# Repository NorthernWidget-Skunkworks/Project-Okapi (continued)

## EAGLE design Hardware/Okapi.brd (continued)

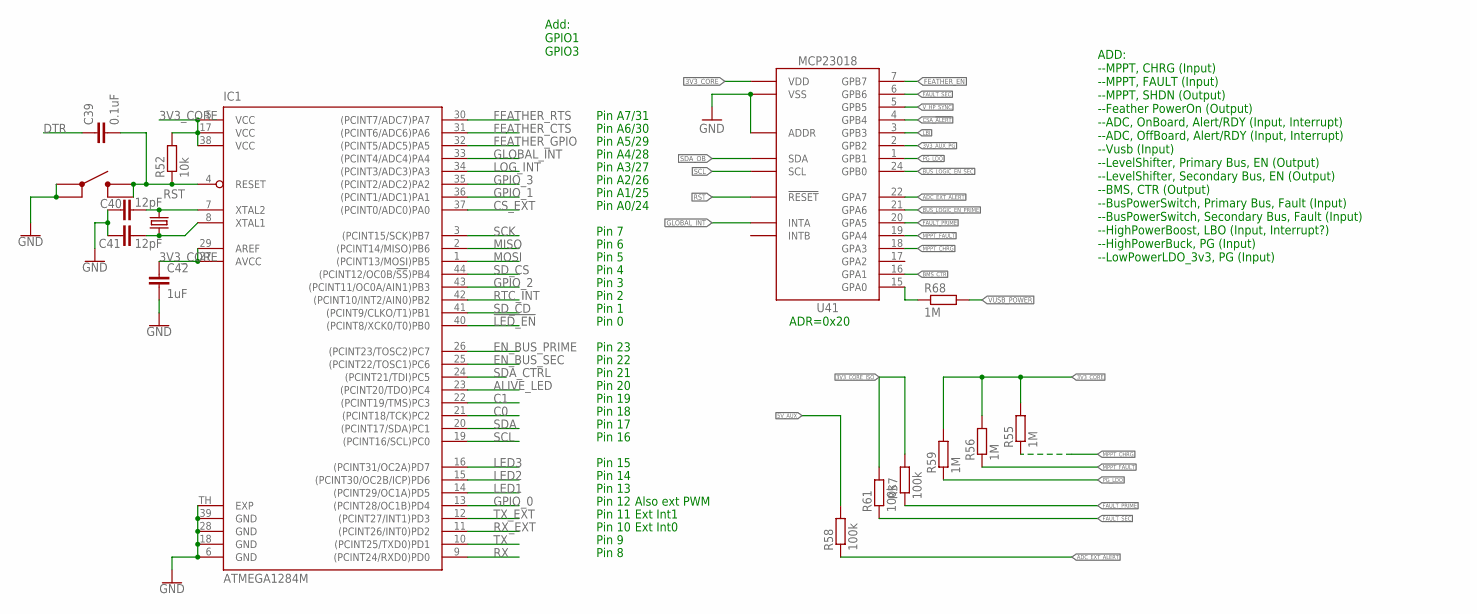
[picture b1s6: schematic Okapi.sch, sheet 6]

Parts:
C39: 0.1uF; C0402
C40, C41: 12pF; C0402; MPN CL10C120JB8NNNC; DIGIKEY 1276-1254-1-ND
C42: 1uF; C0402; MPN CL10B105MO8NNWC; DIGIKEY 1276-6524-1-ND
IC1: ATMEGA1284M; MLF44-TH
R52: 10k; R0402; DIGIKEY 311-10.0KHRCT-ND
R55, R56, R59, R68: 1M; R0402
R57, R58, R61: 100k; R0402
S4: BUTTON4.2X3.2; SWITCH_4.2X3.2
U41: MCP23018QFN; QFN24
XTAL1: CRYSTAL8MHZ5X3.2; CRYSTAL_5X3.2_2-SMD

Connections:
3V3_AUX_PG: U41.2 (GPB2); also elsewhere on the board
3V3_CORE: C42.1, IC1.5 (VCC), IC1.17 (VCC), IC1.27 (AVCC), IC1.29 (AREF), IC1.38 (VCC), R52.2, R55.2, R56.2, R59.2, U41.8 (VDD); also elsewhere on the board
3V3_CORE_ISO: R57.2, R61.2; also elsewhere on the board
5V_AUX: R58.2; also elsewhere on the board
!LED_EN: IC1.40 ((PCINT8/XCK0/T0)PB0); also elsewhere on the board
ADC_EXT_ALERT: R58.1, U41.22 (GPA7); also elsewhere on the board
ALIVE_LED: IC1.23 ((PCINT20/TDO)PC4); also elsewhere on the board
BMS_CTR: U41.16 (GPA1); also elsewhere on the board
BUS_LOGIC_EN_PRIME: U41.21 (GPA6); also elsewhere on the board
BUS_LOGIC_EN_SEC: U41.24 (GPB0); also elsewhere on the board
C0: IC1.21 ((PCINT18/TCK)PC2); also elsewhere on the board
C1: IC1.22 ((PCINT19/TMS)PC3); also elsewhere on the board
CSA_!ALERT: U41.4 (GPB4); also elsewhere on the board
CS_EXT: IC1.37 ((PCINT0/ADC0)PA0); also elsewhere on the board
DTR: C39.1; also elsewhere on the board
EN_BUS_PRIME: IC1.26 ((PCINT23/TOSC2)PC7); also elsewhere on the board
EN_BUS_SEC: IC1.25 ((PCINT22/TOSC1)PC6); also elsewhere on the board
FAULT_PRIME: R57.1, U41.20 (GPA5); also elsewhere on the board
FAULT_SEC: R61.1, U41.6 (GPB6); also elsewhere on the board
FEATHER_CTS: IC1.31 ((PCINT6/ADC6)PA6); also elsewhere on the board
FEATHER_EN: U41.7 (GPB7); also elsewhere on the board
FEATHER_GPIO: IC1.32 ((PCINT5/ADC5)PA5); also elsewhere on the board
FEATHER_RTS: IC1.30 ((PCINT7/ADC7)PA7); also elsewhere on the board
GLOBAL_INT: IC1.33 ((PCINT4/ADC4)PA4), U41.14 (INTA)
GND: C40.1, C41.1, C42.2, IC1.6 (GND), IC1.18 (GND), IC1.28 (GND), IC1.39 (GND), IC1.TH (EXP), S4.1, S4.2, U41.11 (ADDR), U41.23 (VSS), U41.EP (VSS); also elsewhere on the board
GPIO_0: IC1.13 ((PCINT28/OC1B)PD4); also elsewhere on the board
GPIO_1: IC1.36 ((PCINT1/ADC1)PA1); also elsewhere on the board
GPIO_2: IC1.43 ((PCINT11/OC0A/AIN1)PB3); also elsewhere on the board
GPIO_3: IC1.35 ((PCINT2/ADC2)PA2); also elsewhere on the board
LBI: U41.3 (GPB3); also elsewhere on the board
LED1: IC1.14 ((PCINT29/OC1A)PD5); also elsewhere on the board
LED2: IC1.15 ((PCINT30/OC2B/ICP)PD6); also elsewhere on the board
LED3: IC1.16 ((PCINT31/OC2A)PD7); also elsewhere on the board
LOG_INT: IC1.34 ((PCINT3/ADC3)PA3); also elsewhere on the board
MISO: IC1.2 ((PCINT14/MISO)PB6); also elsewhere on the board
MOSI: IC1.1 ((PCINT13/MOSI)PB5); also elsewhere on the board
MPPT_CHRG: R55.1, U41.18 (GPA3); also elsewhere on the board
MPPT_FAULT: R56.1, U41.19 (GPA4); also elsewhere on the board
unnamed: R68.1, U41.15 (GPA0)
unnamed: C40.2, IC1.7 (XTAL2), XTAL1.OSC2 (2)
unnamed: C41.2, IC1.8 (XTAL1), XTAL1.OSC1 (1)
PG_LDO: R59.1, U41.1 (GPB1); also elsewhere on the board
RST: C39.2, IC1.4 (RESET), R52.1, S4.3 (4), S4.4 (3), U41.12 (!RESET); also elsewhere on the board
RTC_INT: IC1.42 ((PCINT10/INT2/AIN0)PB2); also elsewhere on the board
RX: IC1.9 ((PCINT24/RXD0)PD0); also elsewhere on the board
RX_EXT: IC1.11 ((PCINT26/INT0)PD2); also elsewhere on the board
SCK: IC1.3 ((PCINT15/SCK)PB7); also elsewhere on the board
SCL: IC1.19 ((PCINT16/SCL)PC0), U41.9 (SCL); also elsewhere on the board
SDA: IC1.20 ((PCINT17/SDA)PC1); also elsewhere on the board
SDA_CTRL: IC1.24 ((PCINT21/TDI)PC5); also elsewhere on the board
SDA_OB: U41.10 (SDA); also elsewhere on the board
SD_CD: IC1.41 ((PCINT9/CLKO/T1)PB1); also elsewhere on the board
SD_CS: IC1.44 ((PCINT12/OC0B/!SS!)PB4); also elsewhere on the board
TX: IC1.10 ((PCINT25/TXD0)PD1); also elsewhere on the board
TX_EXT: IC1.12 ((PCINT27/INT1)PD3); also elsewhere on the board
VUSB_POWER: R68.2; also elsewhere on the board
V_HP_SYNC: U41.5 (GPB5); also elsewhere on the board

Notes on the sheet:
Pin 12
Pin A7/31
Pin A6/30
Pin A5/29
Pin A4/28
Pin 15
Pin 23
Pin A3/27
Also ext PWM
Pin 19
Pin 14
Pin 13
Pin 3
Pin 2
Pin 1
Pin 4
Pin A0/24
Pin A1/25
Pin A2/26
Pin 20
Pin 11
Pin 10
Pin 9
Pin 8
Pin 16
Pin 17
Pin 18
Pin 21
Pin 22
Pin 0
Pin 5
Pin 6
Pin 7
Ext Int1
Ext Int0
Add: GPIO1 GPIO3
ADD: --MPPT, CHRG (Input) --MPPT, FAULT (Input) --MPPT, SHDN (Output) --Feather PowerOn (Output) --ADC, OnBoard, Alert/RDY (Input, Interrupt) --ADC, OffBoard, Alert/RDY (Input, Interrupt) --Vusb (Input) --LevelShifter, Primary Bus, EN (Output) --LevelShifter, Secondary Bus, EN (Output) --BMS, CTR (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
ADR=0x20

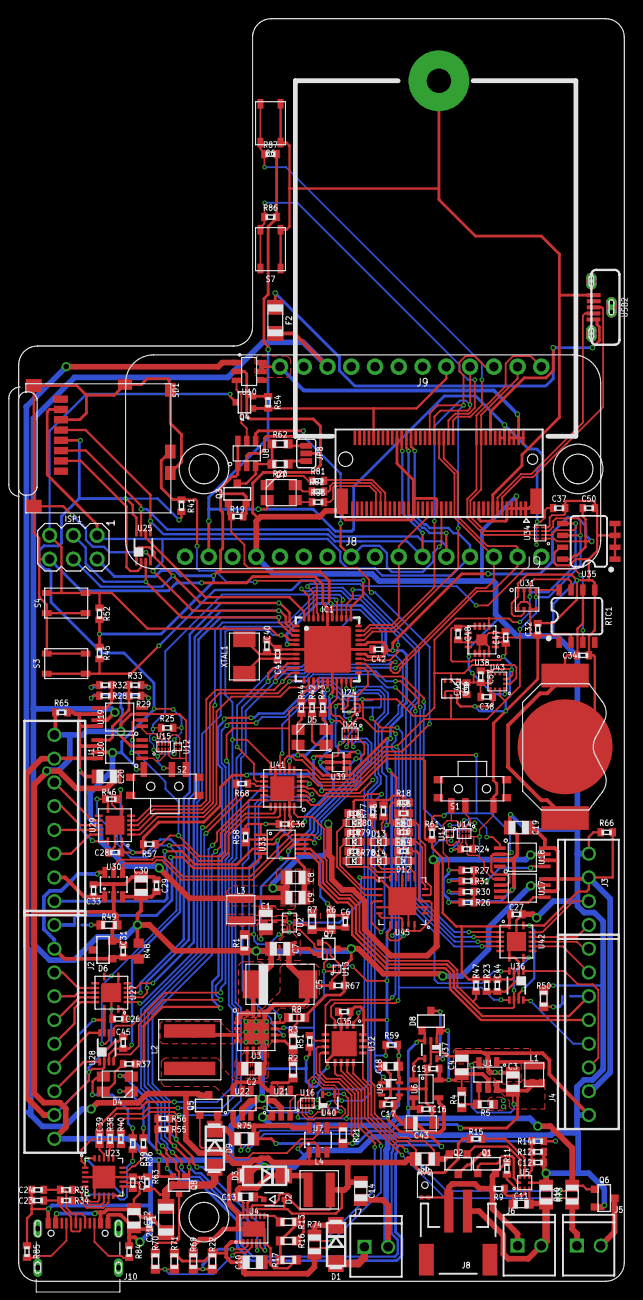
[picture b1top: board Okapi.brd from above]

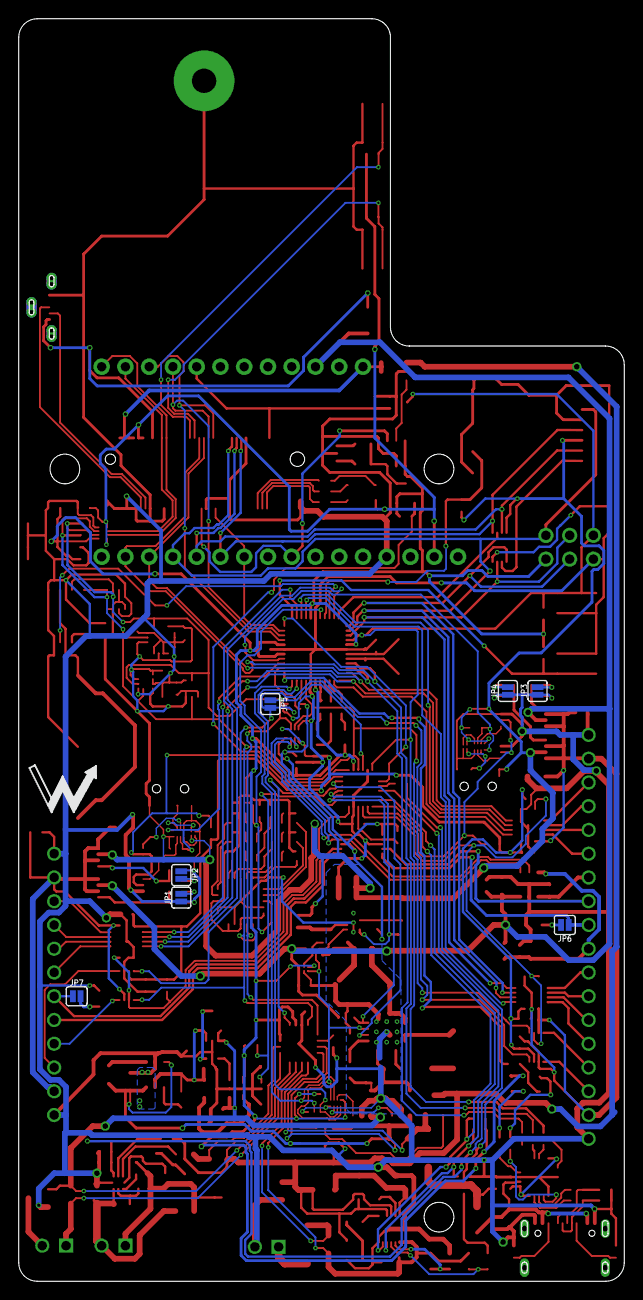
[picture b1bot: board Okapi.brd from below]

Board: 2 copper layers, 64.8 x 135.0 mm, 252 parts (8 on the bottom side), 207 nets.

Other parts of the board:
U$4: NWLOGO_MED

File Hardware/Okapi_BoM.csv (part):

Qty,Value,Device,Package,Parts,Description,DIGIKEY,DISP,MF,MFP,MOUSER,MPN,PROD_ID,VALUE,VALUE_PART
3,,CONN_022.54_SCREW,1X02_2.54_SCREWTERM,"J5, J6, J7",Genaric 2 terminal header,ED10561-ND,,OnShore,,,OSTVN02A150,,,
1,,CONN_102.54_SCREW,1X10_SCREW,J2,Genaric 10 terminal header,ED10567-ND,,On Shore,,,OSTVN10A150,,,
1,,DIODEDO-214AC,DO214AC,D9,Genaric Diode,B340A-FDICT-ND,,Diodes Incorporated,,,B340A-13-F,,,
2,,DIODEDO-214AC,DO214AC,"D1, D3",Genaric Diode,CMSH3-40MATR13CT-ND,,Central Semiconductor,,,CMSH3-40MA TR13,,,
1,,DIODESOD-323,SOD323-R,D2,Genaric Diode,CMDSH2-3CT-ND,,Central Semiconductor,,,CMDSH2-3 TR,,,
1,,JST_2MM_MALE,JST-2-SMD,J8,JST 2MM MALE RA CONNECTOR,455-1749-1-ND,,JST,,,S2B-PH-SM4-TB(LF)(SN),,,
2,,LM40402.5,SOT23-3,"D6, D7",LM4040 - Precision Micropower Shunt Voltage Referance,576-1047-1-ND,,Microchip,,,LM4040DYM3-2.5-TR,,,
1,,LT3652DD,DFN_12_3X3,U4,LT3652 - Power Tracking Battery Charger for Solar Power (MPPT),LT3652EDD#PBF-ND,,LT,,,LT3652EDD#PBF,,,
3,,MOUNTING_HOLE4_NP,4_40,"H1, H2, H3",Genaric Mechanical Mounting Hole,,,,,,,,,
1,,R-EU_10KR0402,R0402,R54,"RESISTOR, European symbol",311-10.0KHRCT-ND,,Yageo,,,RC0603FR-0710KL,,,10k
19,0.1uF,C-EU0.1UFC0402,C0402,"C12, C17, C21, C25, C26, C27, C28, C29, C31, C32, C33, C34, C35, C36, C37, C38, C39, C44, C45","CAPACITOR, European symbol",490-4759-1-ND,,Murata,,,GCM155R71C104KA55D,,,
2,0.22uF,C-EU0.22UFC0402,C0402,"C15, C16","CAPACITOR, European symbol",490-12265-1-ND,,Murata,,,GRT155R61E224KE01D,,,
2,1.62M,R-EU_1.62MR0603,R0603,"R2, R4","RESISTOR, European symbol",RMCF0603FT1M62CT-ND,,Stackpole,,,RMCF0603FT1M62,,,1.62M
1,100R,R-EU_100R0402,R0402,R14,"RESISTOR, European symbol",311-100LRCT-ND,,Yageo,,,RC0402FR-07100RL,,,100
6,100k,R-EU_100KR0402,R0402,"R23, R57, R58, R60, R61, R63","RESISTOR, European symbol",311-100KLRCT-ND,,Yageo,,,RC0402FR-07100KL,,,100k
1,100k,R-EU_100KR0603,R0603,R69,"RESISTOR, European symbol",RC0402FR-071ML,,Yageo,,,RC0603FR-07100KL,,,100k
1,100uF,CTANT_EU1206,C1206_TANT,C43,Genaric Tantalum Capacitor,718-1921-1-ND,,Vishay Sprague,,,TL8A0107M010D,,,
8,10k,R-EU_10KR0402,R0402,"R24, R25, R41, R45, R46, R47, R52, R67","RESISTOR, European symbol",311-10.0KHRCT-ND,,Yageo,,,RC0603FR-0710KL,,,10k
2,10k,R-EU_P10KR0603,R0603,"R49, R50","RESISTOR, European symbol",P10KDBCT-ND,,Panasonic,,,ERA-3AEB103V,,,10k
5,10uF,C-EU10UFC0805,C0805,"C3, C4, C14, C22, C30","CAPACITOR, European symbol",490-6473-6-ND,,Murata,,,GRM21BR61C106KE15K,,,
1,10uH,INDUCTORXHMI_6.65X6.45,WE-XHMI(6.65X6.45),L2,Genaric inductor,732-10707-1-ND,,Wurth,,,74439346100,,,
1,120k,R-EU_120KR0402,R0402,R19,"RESISTOR, European symbol",311-120KLRCT-ND,,Yageo,,,RC0402FR-07120KL,,,120k
2,12pF,C-EU12PFC0402,C0402,"C23, C24","CAPACITOR, European symbol",445-5585-1-ND,,TDK,,,CGA2B2C0G1H120J050BA,,,
2,12pF,C-EU12PFC0402,C0402,"C40, C41","CAPACITOR, European symbol",1276-1254-1-ND,,Samsung,,,CL10C120JB8NNNC,,,
1,130k,R-EU_130KR0603,R0603,R20,"RESISTOR, European symbol",311-130KHRCT-ND,,Yageo,,,RC0603FR-07130KL,,,130k
1,143k,R-EU_143KR0603,R0603,R22,"RESISTOR, European symbol",311-143KHRCT-ND,,Yageo,,,RC0603FR-07143KL,,,143k
2,180k,R-EU_180KR0402,R0402,"R65, R66","RESISTOR, European symbol",311-180KLRCT-ND,,Yageo,,,RC0402FR-07180KL,,,180k
4,180k,R-EU_180KR0603,R0603,"R1, R5, R7, R8","RESISTOR, European symbol",P180KHCT-ND,,Panasonic,,,ERJ-3EKF1803V,,,180k
1,182k,R-EU_182KR0603,R0603,R13,"RESISTOR, European symbol",P182KHCT-ND,,Panasonic,,,ERJ-3EKF1823V,,,182k
6,1M,R-EU_1MR0402,R0402,"R53, R55, R56, R59, R64, R68","RESISTOR, European symbol",311-1.00MLRCT-ND,,Yageo,,,RC0402FR-071ML,,,1M
1,1M,R-EU_1MR0603,R0603,R71,"RESISTOR, European symbol",P1.00MHCT-ND,,Panasonic,,,ERJ-3EKF1004V,,,1M
1,1k,R-EU_1KR0402,R0402,R12,"RESISTOR, European symbol",311-1.00KLRCT-ND,,Yageo,,,RC0402FR-071KL,,,1k
1,1uF,C-EU0.1UFC0402,C0402,C42,"CAPACITOR, European symbol",1276-6524-1-ND,,Samsung,,,CL10B105MO8NNWC,,,
2,1uF,C-EU1UFC0603,C0603,"C11, C13","CAPACITOR, European symbol",490-10479-1-ND,,Murata,,,GRM188R61C105KA12D,,,
1,1uH,INDUCTORLQS_3X3,WE-LQS(3X3),L3,Genaric inductor,732-5491-1-ND,,Wurth,,,74404032010,,,
1,20,R-EU_20R0402,R0402,R11,"RESISTOR, European symbol",311-20LRCT-ND,,Yageo,,,RC0402FR-0720RL,,,20
1,200k,R-EU_200KR0603,R0603,R70,"RESISTOR, European symbol",311-200KHRCT-ND,,Yageo,,,RC0603FR-07200KL,,,200k
1,20k,R-EU_20KR0603,R0603,R51,"RESISTOR, European symbol",311-20.0KHRCT-ND,,Yageo,,,RC0603FR-0720KL,,,20k
1,220uF,CTANT_EU2917,C2917,C5,Genaric Tantalum Capacitor,478-5408-1-ND,,AVX,,,TPSY227K010R0100,,,
7,22uF,C-EU22UFC0805,C0805,"C2, C7, C8, C9, C10, C19, C20","CAPACITOR, European symbol",490-9952-1-ND,,Murata,,,GRM219R61C226ME15L,,,
2,27,R-EU_27R0402,R0402,"R34, R35","RESISTOR, European symbol",YAG3086CT-ND,,Yageo,,,RC0402FR-0727RL,,,27
4,287R,R-EU_232R0402,R0402,"R26, R27, R28, R29","RESISTOR, European symbol",YAG3063CT-ND,,Yageo,,,RC0402FR-07232RL,,,232
4,287R,R-EU_453R0402,R0402,"R30, R31, R32, R33","RESISTOR, European symbol",YAG3165CT-ND,,Yageo,,,RC0402FR-07453RL,,,453
3,2N7002,MOSFET-NCH-2N7002PW,SOT323,"Q4, Q7, Q8",N-channel MOSFETs,2N7002W-FDICT-ND,,Diodes Incorporated,,,2N7002W-7-F,TRANS-11151,2N7002,
1,2k,R-EU_2KR0402,R0402,R15,"RESISTOR, European symbol",311-2KLRCT-ND,,Yageo,,,RC0402FR-072KL,,,2k
2,330,R-EU_330R0402,R0402,"R37, R39","RESISTOR, European symbol",311-330HRCT-ND,,Yageo,,,RC0603FR-07330RL,,,330
1,330,R-EU_330R0402,R0402,R9,"RESISTOR, European symbol",311-330LRCT-ND,,Yageo,,,RC0402FR-07330RL,,,330
6,330,R-EU_330R0402,R0402,"R36, R38, R40, R42, R43, R44","RESISTOR, European symbol",311-330LRCT-ND,,Yageo,,,RC0603FR-07330RL,,,330
1,10k,R-EU_10K0603,R0603,R48,"RESISTOR, European symbol",311-10.0KHRCT-ND,,Yageo,,,RC0603FR-0710KL,,,10k
2,330k,R-EU_330KR0603,R0603,"R17, R62","RESISTOR, European symbol",P330KHCT-ND,,Panasonic,,,ERJ-3EKF3303V,,,330k
1,360k,R-EU_360KR0603,R0603,R3,"RESISTOR, European symbol",311-360KHRCT-ND,,Yageo,,,RC0603FR-07360KL,,,360k
1,3m,R-EU_0.003R0805,R0805,R10,"RESISTOR, European symbol",RHM.003AJCT-ND,,Rohm,,,PMR10EZPFV3L00,,,
1,4.7uF,C-EU4.7UFC0805,C0805,C1,"CAPACITOR, European symbol",399-7415-1-ND,,Kemet,,,C0805C475K4RACTU,,,
1,4.7uH,INDUCTORMAIA_4.1X4.1,WE-MAIA(4.1X4.1),L4,Genaric inductor,732-11316-1-ND,,Wurth,,,78438356047,,,
1,470k,R-EU_470KR0603,R0603,R21,"RESISTOR, European symbol",311-470KGRCT-ND,,Yageo,,,RC0603JR-07470KL,,,470k
1,50m,R-EU_0.05R0805,R0805,R18,"RESISTOR, European symbol",P50LLCT-ND,,Panasonic,,,ERJ-L06KF50MV,,,
1,6.8uH,INDUCTOR1008,1008,L1,Genaric inductor,732-4849-1-ND,,Wurth,,,74438323068,,,
1,68pF,C-EU68PFC0402,C0402,C6,"CAPACITOR, European symbol",732-7474-1-ND,,Wurth,,,8.85012E+11,,,
1,820k,R-EU_820KR0603,R0603,R6,"RESISTOR, European symbol",311-820KGRCT-ND,,Yageo,,,RC0603JR-07820KL,,,820k
1,91k,R-EU_91KR0603,R0603,R16,"RESISTOR, European symbol",P91.0KHCT-ND,,Panasonic,,,ERJ-3EKF9102V,,,91k
2,ADS1115,ADS1115,VSSOP_10,"U32, U33",ADS1115 - Sigma Delta ADC,296-38849-1-ND,,TI,,,ADS1115IDGSR,,,
1,ATMEGA1284M,ATMEGA1284M,MLF44-TH,IC1,8-bit Microcontroller with 128K Bytes In-System Programmable Flash,ATMEGA1284P-MURCT-ND,,Atmel,,,ATMEGA1284P-MUR,,,
1,AVRISP-6,AVRISP-6,AVRISP,ISP1,AVR ISP HEADER,609-3234-ND,,Amphenol,,,67997-206HLF,,,
1,BAT54C,BAT54C,SOT23-3,D8,BAT54C,BAT54CLT1GOSCT-ND,,ON Semiconductor,BAT54CLT1G,,,,,
1,BATTERY_COIN12MM,BATTERY_COIN12MM,LINX_BAT-HLD-012-SMT,BT1,Coin Cell Battery Holder,BAT-HLD-012-SMT-ND,,Linx,,,BAT-HLD-012-SMT,,,
1,BME280,BME280,BME280,U31,BME280 - Combined Digital Humidity and Pressure Sensor,828-1063-1-ND,BME280,Bosch,,,BME280,,,
1,BQ2980RUG,BQ2980RUG,RUG_S-PQFP-N8,U5,"BQ2980 - Voltage, Current, Temperature Protectors with an Integrated High-Side NFET (BMS)",296-47578-1-ND,,TI,,595-BQ298000RUGT,BQ298000RUGT,,,
1,BUTTON2.6X1.6,BUTTON2.6X1.6,SWITCH_2.6X1.6,S5,Genaric SPST Pushbutton,P19888CT-ND,,Panasonic ,,,EVP-BB2A9B000,,,
2,BUTTON4.2X3.2,BUTTON4.2X3.2,SWITCH_4.2X3.2,"S3, S4",Genaric SPST Pushbutton,CKN10504CT-ND,,C&K,,,PTS810 SJG 250 SMTR LFS,,,
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
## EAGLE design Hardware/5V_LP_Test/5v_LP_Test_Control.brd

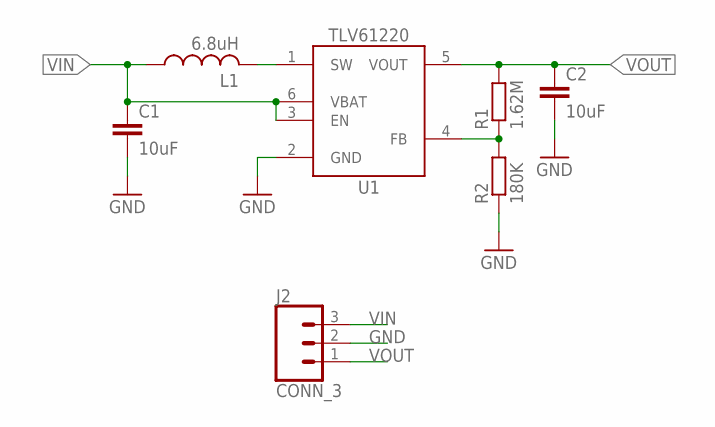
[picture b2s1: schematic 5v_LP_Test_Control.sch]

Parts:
C1, C2: 10uF; C0805
J2: CONN_3; 1X03
L1: 6.8uH; 1008
R1: 1.62M; R0603
R2: 180K; R0603
U1: TLV61220DBV; DBV_R-PDSO-G6

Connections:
GND: C1.2, C2.2, J2.2, R2.1, U1.2 (GND)
unnamed: R1.1, R2.2, U1.4 (FB)
unnamed: L1.2, U1.1 (SW)
VIN: C1.1, J2.3, L1.1, U1.3 (EN), U1.6 (VBAT)
VOUT: C2.1, J2.1, R1.2, U1.5 (VOUT)

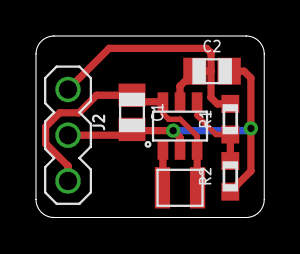
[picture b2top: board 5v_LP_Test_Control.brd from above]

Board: 2 copper layers, 12.7 x 10.1 mm, 7 parts (0 on the bottom side), 5 nets.

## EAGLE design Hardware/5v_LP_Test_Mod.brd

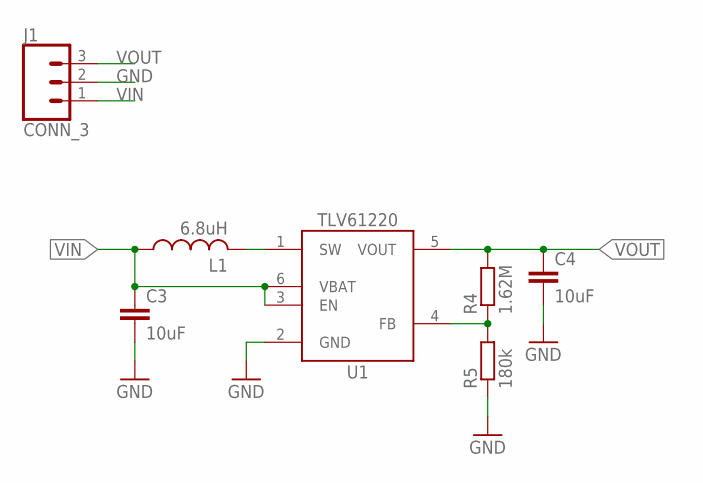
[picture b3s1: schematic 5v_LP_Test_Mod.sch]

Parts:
C3, C4: 10uF; C0805
J1: CONN_3; 1X03
L1: 6.8uH; 1008; MPN 74438323068; DIGIKEY 732-4849-1-ND
R4: 1.62M; R0603
R5: 180k; R0603
U1: TLV61220DBV; DBV_R-PDSO-G6

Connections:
GND: C3.2, C4.2, J1.2, R5.1, U1.2 (GND)
unnamed: R4.1, R5.2, U1.4 (FB)
unnamed: L1.2, U1.1 (SW)
VIN: C3.1, J1.1, L1.1, U1.3 (EN), U1.6 (VBAT)
VOUT: C4.1, J1.3, R4.2, U1.5 (VOUT)

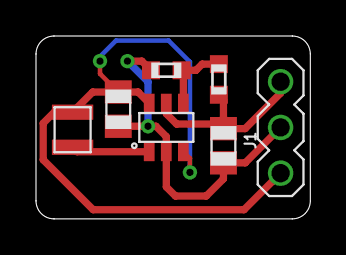
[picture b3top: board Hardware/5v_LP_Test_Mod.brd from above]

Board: 2 copper layers, 15.2 x 10.2 mm, 7 parts (0 on the bottom side), 5 nets.

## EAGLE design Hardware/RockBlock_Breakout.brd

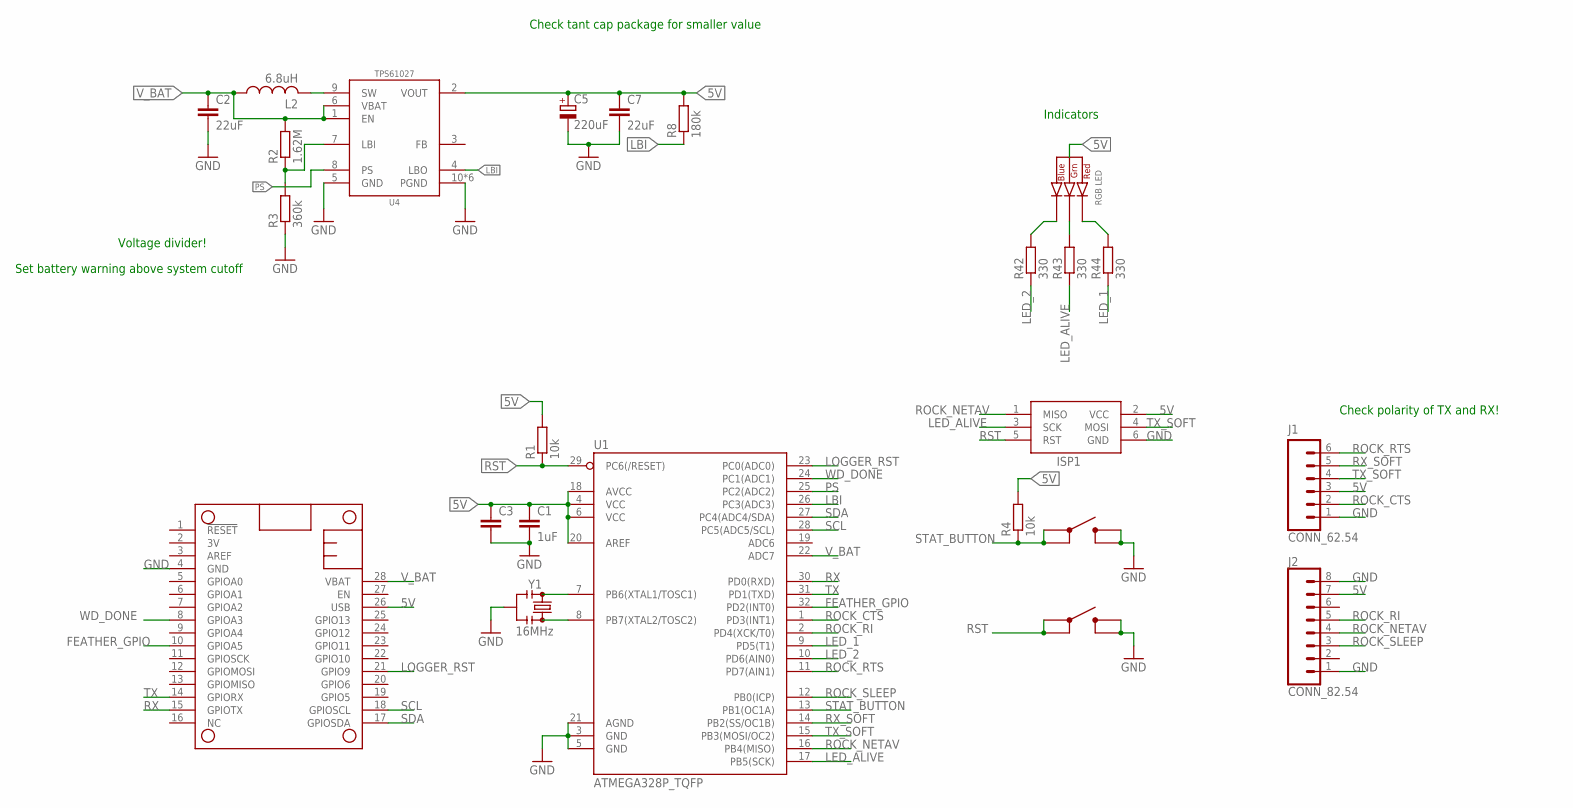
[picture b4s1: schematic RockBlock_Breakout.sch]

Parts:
C1: 1uF; C0603
C2, C7: 22uF; C0805
C3: C-EUC0402; C0402
C5: 220uF; C2917; MPN TPSY227K010R0100; DIGIKEY 478-5408-1-ND
D5: CLVBA-FKA
ISP1: AVRISP-6; AVRISP
J1: CONN_62.54; 1X06
J2: CONN_82.54; 1X08
L2: 6.8uH; WE-TPC(4.8X4.8); MPN 744042006; DIGIKEY 732-1023-1-ND
MS1: FEATHERWINGLAYOUT; FEATHERWING_MIN
R1, R4: 10k; R0402
R2: 1.62M; R0603
R3: 360k; R0603
R8: 180k; R0603
R42, R43, R44: 330; R0402; MPN RC0603FR-07330RL
S1, S2: BUTTON4.2X3.2; SWITCH_4.2X3.2
U1: ATMEGA328P_TQFP; TQFP32-08
U4: TPS61027DRC; DRC0010J
Y1: 16MHz; RESONATOR-SMD-3.2X1.3

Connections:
5V: C1.1, C3.1, C5.+, C7.1, D5.2 (ANODE), ISP1.2 (VCC), J1.3, J2.7, MS1.26 (USB), R1.2, R4.2, R8.2, U1.4 (VCC), U1.6 (VCC), U1.18 (AVCC), U1.20 (AREF), U4.2 (VOUT)
FEATHER_GPIO: MS1.10 (GPIOA5), U1.32 (PD2(INT0))
GND: C1.2, C2.2, C3.2, C5.-, C7.2, ISP1.6 (GND), J1.1, J2.1, J2.8, MS1.4 (GND), R3.1, S1.3 (4), S1.4 (3), S2.3 (4), S2.4 (3), U1.3 (GND), U1.5 (GND), U1.21 (AGND), U4.5 (GND), U4.10 (PGND), U4.EP@1 (PGND), U4.EP@2 (PGND), U4.EP@3 (PGND), U4.EP@4 (PGND), U4.EP@5 (PGND), Y1.2
LBI: R8.1, U1.26 (PC3(ADC3)), U4.4 (LBO)
LED_1: R44.1, U1.9 (PD5(T1))
LED_2: R42.1, U1.10 (PD6(AIN0))
LED_ALIVE: ISP1.3 (SCK), R43.1, U1.17 (PB5(SCK))
LOGGER_RST: MS1.21 (GPIO9), U1.23 (PC0(ADC0))
unnamed: U1.7 (PB6(XTAL1/TOSC1)), Y1.1
unnamed: U1.8 (PB7(XTAL2/TOSC2)), Y1.3
unnamed: R2.1, R3.2, U4.7 (LBI)
unnamed: L2.2, U4.9 (SW)
unnamed: D5.3 (BLUE_CATH), R42.2
unnamed: D5.4 (GREEN_CATH), R43.2
unnamed: D5.1 (RED_CATH), R44.2
PS: U1.25 (PC2(ADC2)), U4.8 (PS)
ROCK_CTS: J1.2, U1.1 (PD3(INT1))
ROCK_NETAV: ISP1.1 (MISO), J2.4, U1.16 (PB4(MISO))
ROCK_RI: J2.5, U1.2 (PD4(XCK/T0))
ROCK_RTS: J1.6, U1.11 (PD7(AIN1))
ROCK_SLEEP: J2.3, U1.12 (PB0(ICP))
RST: ISP1.5 (RST), R1.1, S2.1, S2.2, U1.29 (PC6(/RESET))
RX: MS1.15 (GPIOTX), U1.30 (PD0(RXD))
RX_SOFT: J1.5, U1.14 (PB2(SS/OC1B))
SCL: MS1.18 (GPIOSCL), U1.28 (PC5(ADC5/SCL))
SDA: MS1.17 (GPIOSDA), U1.27 (PC4(ADC4/SDA))
STAT_BUTTON: R4.1, S1.1, S1.2, U1.13 (PB1(OC1A))
TX: MS1.14 (GPIORX), U1.31 (PD1(TXD))
TX_SOFT: ISP1.4 (MOSI), J1.4, U1.15 (PB3(MOSI/OC2))
V_BAT: C2.1, L2.1, MS1.28 (VBAT), R2.2, U1.22 (ADC7), U4.1 (EN), U4.6 (VBAT)
WD_DONE: MS1.8 (GPIOA3), U1.24 (PC1(ADC1))

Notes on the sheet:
Voltage divider!
Set battery warning above system cutoff
Indicators
Check polarity of TX and RX!
Check tant cap package for smaller value

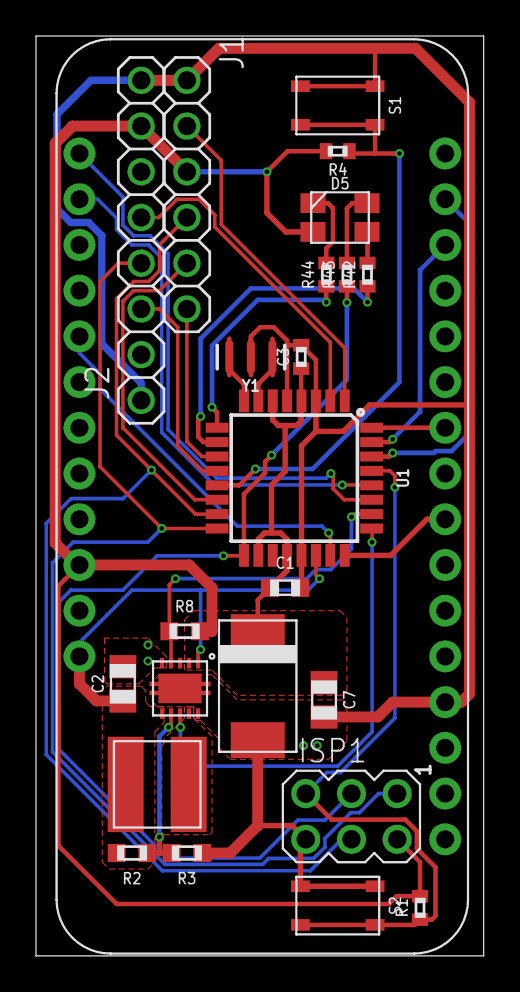
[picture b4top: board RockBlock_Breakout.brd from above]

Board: 2 copper layers, 24.9 x 51.1 mm, 24 parts (0 on the bottom side), 31 nets.

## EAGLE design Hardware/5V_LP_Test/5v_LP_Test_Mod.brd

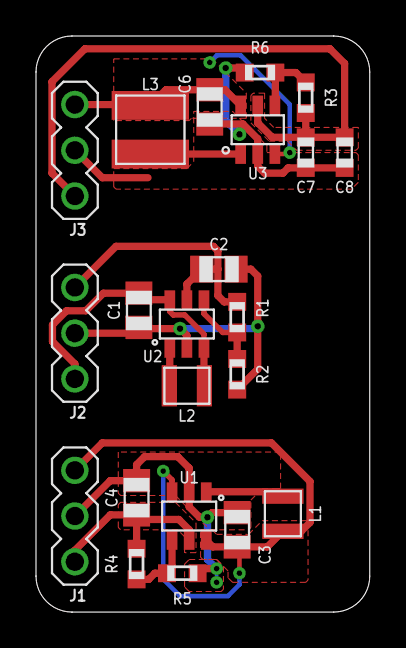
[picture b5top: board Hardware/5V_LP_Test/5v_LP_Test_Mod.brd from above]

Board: 2 copper layers, 18.5 x 32.0 mm, 22 parts (0 on the bottom side), 15 nets.

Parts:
C1, C2, C3, C4: 10uF; C0805
C6: C0805
C7, C8: C0603
J1, J2, J3: CONN_3; 1X03
L1, L2: 6.8uH; 1008
L3: WE-TPC(3.8X3.8)
R1, R4: 1.62M; R0603
R2: 180K; R0603
R3, R6: R0603
R5: 180k; R0603
U1, U2: TLV61220DBV; DBV_R-PDSO-G6
U3: TPS61070DDC; DDC_R-PDSO-G6

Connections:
GND: C3.2, C4.2, J1.2, R5.1, U1.2
GND1: C1.2, C2.2, J2.2, R2.1, U2.2
GND2: C6.2, C7.2, C8.2, J3.2, R6.1, U3.2
unnamed: R1.1, R2.2, U2.4
unnamed: L3.2, U3.1
unnamed: L2.2, U2.1
unnamed: R3.1, R6.2, U3.4
unnamed: R4.1, R5.2, U1.4
unnamed: L1.2, U1.1
VIN: C3.1, J1.1, L1.1, U1.3, U1.6
VIN1: C1.1, J2.3, L2.1, U2.3, U2.6
VIN2: C6.1, J3.1, L3.1, U3.3, U3.6
VOUT: C4.1, J1.3, R4.2, U1.5
VOUT1: C2.1, J2.1, R1.2, U2.5
VOUT2: C7.1, C8.1, J3.3, R3.2, U3.5

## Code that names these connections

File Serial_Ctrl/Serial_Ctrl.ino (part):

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boolean Debug = false; //FIX!!
char ReadArray[25] = {0};

const uint8_t C1 = 19; //Control pins for V_HP
const uint8_t C0 = 18;

const uint8_t EN_BUS_PRIME = 23;  //Power enable lines for buses
const uint8_t EN_BUS_SEC = 22;

const uint8_t GPIO[4] = {12, 25, 3, 26}; //GPIO pins 0~3, 0,1 on primary bus, 2,3 on secondary bus. 0 and 2 PWM capable

const uint8_t Global_Int = 28; //Global interrupt from IO Expander
const uint8_t Log_Int = 27; //Interrupt for logging event

////////////////////////////////////SD////////////////////////////////////////
const uint8_t SD_CS = 4; //Define chip select for SD card
char FileNameC[11]; //Used for file handling
boolean SD_Init = false;

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boolean TestSD()
{
  boolean SDError = false;
  pinMode(SD_CS, OUTPUT);
  SPI.setDataMode(SPI_MODE0);
  SPI.setClockDivider(SPI_CLOCK_DIV2); //Sts SPI clock to 4 MHz for an 8 MHz system clock

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
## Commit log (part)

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2018-10-18 Added Creative Commons Licence
2018-10-18 Added pin connections document
2018-10-23 Created schematic and board, beginning ECAD population
2018-10-25 Continued schematic additions, prelim part placement
2018-10-26 Preliminary power section layout
2018-10-27 Continued layout, board size change
2018-10-29 Continued layout, major of power and prime bus done
2018-10-30 Continued layout, majority of secondary bus, low power
2018-10-30 Added OR Controller simulation
    Also updated gitignore to prevent issues with LTSpice stuff
2018-10-30 Continued layout, starting on SD and Feather header
2018-11-01 Layout tentative completed, sent to DFM check
    Layout complete for v0.0, pending final triple check, sent to DFM check to verify manufacture issues. Ready for final external review.
2018-11-01 Added PDFs of prelim v0.0 schematic
2018-11-01 Added board PDFs of prelim v0.0
2018-11-02 Minor board edits, updated gerbers, pending DFM
2018-11-07 Updated BOM info
    Added info to schematic to support auto-generating BOM
2018-11-10 Added very early RockBlock breakout
2018-11-13 Preliminary layout of RockBlock Breakout
    Still needs cleanup and some verification
2018-11-13 Aligned buttons on RockBlock breakout
2018-11-15 Routing cleanup
2018-11-16 Created serial control demo
    Still need to develop serial control demo...
2018-11-19 Built Serial Ctrl script
    Flushed out serial ctrl test script to allow for pin by pin and sub module testing and control
2018-11-19 Updated inductor L2 layout
    Fixed size and part number of inductor to match XHMI layout
2018-11-20 First round of fixes to hardware
    changed SD card holder, power switches, power switch topology, add pull up resistors to IO expander, to allow for new non-internal pull up module, added some silkscreen, added 3v3 core I2C pullups
2018-11-20 Layout fixes
    Improvements and cleanup in the layout, should get final review before being sent out to fab
2018-11-26 Generated Gerbers, Minor Updates
    v0.1 Sent to fab
2018-11-29 Added dimensions, updated part numbers
2018-11-30 Fixed part value for TCA9555 (to TCA9535)
2019-01-09 Updated pin connections doc
2019-01-10 Fixed MPPT set resistors
    Fixed the order of the MPPT voltage set resistors. Correct values were used, but in the wrong orientation, this has been corrected
2019-01-19 Fixed message format in `Serial_Ctrl`
2019-02-07 Added 5v LP control test board
2019-02-08 Added 5v LP modified test board
2019-02-09 Initial schematic updated for v0.2
    First round of updates to schematic for v0.2 update, needs verification before layout begins
2019-02-12 Initial layout update for v0.2
    Layout mainly complete, review required, need to delete some extraneous parts
2019-02-12 Added gerbers for modified 5v test board
2019-02-12 Removed extraneous protection circuit
    Removed deprecated MOSFET protection circuit on ADC
2019-02-14 Updated test boards for VolteraV1
    Attempted to maximize compatibility with Voltera V1 system
2019-02-16 Updates to 5v test board
    Added additional converter to 5v test setup, also condensed all units onto a single board and generated gerbers for compatibility with Sunstone PCB
2019-02-20 Added updated gerbers for Sunstone fab
2019-03-14 Minor cleanup
    Top layer checked and verified, bottom layer still needs cleanup and verification, also update version number!
2019-03-16 Minor cleanup and gerber generation, ready for v0.2
2019-03-21 Improved paste layout, generated stencil gerbers
    Updated the paste distribution on several parts, generated gerbers for the stencil
2019-06-05 Remove I2C disable with power off
2019-06-06 Initial updates for v0.3
    Additional routing required, need to add ADC switch enable, need to add efficiency modification to mppt
2019-06-06 Layout updates, cleanup required, minor testing
2019-06-06 Continued layout, generated gerbers
    Improved layout, generated gerbers, final design review before send to fab
2019-07-31 Naming/part cleanup
2019-07-31 Added testing files for Boron and Resnik
    Added multiple testing files, omitted compiled binaries for Boron
2019-08-13 Hardware fixes, review and verification required, gerber generated
    Gerber generated and sent to DFM, verification and review required
2019-08-14 Silk screen edits, generated gerbers, v0.4 send to fab
2019-08-14 Minor value changes, generated BoM for quote generation
2019-08-22 Added Ref ID images, updated BoM for new parts, added pick and place
2019-11-02 Added reference designators, cleanup
2019-11-02 Added Boron test files
2020-02-13 Update to fix issue #6, start of v0.5
    Fixed battery parasitic draw into ADC issue be connecting ADC to battery through protection circuit, preventing the parasitic draw from discharging the battery below the UVLO voltage
2020-04-25 Remove old Gerber zips
2020-04-25 Current BoM only; no versions in file names
2020-04-25 5V_LP_Test board to subdirectory
2020-04-25 v0.0; old
2020-04-25 Old code for renumbering pins; keep in archive only
2020-04-30 Construction and user's guide, first draft
2020-04-30 Images for new documentation
2020-04-30 Battery mount and strap (primary AA)
2020-04-30 PolyCase P/N for fitting box
2020-04-30 CC BY-SA 4.0
2020-05-01 GPL for code
2020-05-03 Label all jumpers: text and diagrams
2020-05-07 Add solder wick to supplies list
2020-05-27 Materials: screws, power system
2020-05-27 Cable gland link (ElecDirect); formatting
2020-06-04 Adafruit plug for solar panel
2020-06-18 Sources of support
2020-06-18 Remove blank line between images
2020-06-18 USGS Innovation Center
2020-06-18 Fix USGS logo
2020-10-01 Updated fastener BOM and links
2020-10-02 Added Mounting Plate drawings
2020-10-02 Updated Materials list on Readme
    Added mounting plate link and changed Batteries to Power section, added link to AA battery pack
2020-10-02 Updated Resnik mounting screws
2020-10-03 Updated mounting plate drawings
    Updated mounting plate drawings to account for battery packs rotated 90 degrees, Resnik board centered.
2020-10-26 Added STEP file of Mounting Plate v1.3
2020-10-26 Rename Mounting Plate.step to Resnik Mounting Plate v1.3.step
2020-10-27 Mounting plate for milling: routing outside the lines in Easel should work
2020-11-01 Spaces --> Underscores in file names
2020-11-01 AA backup battery box (x3, 3D print files)
2020-11-01 Battery mount for small Margay box
2020-11-01 AA battery mount for 3D printing
2020-11-01 Update to Resnik large-box small-holder with countersunk screw holes
2021-03-02 DOI badge
2021-03-05 parallel --> series typo fix
2021-03-10 On-board I2C, SPI, and UART devices
2021-03-11 Polishing the Status Codes section a bit for consistency
2021-03-11 typo
2021-07-05 vim swapfiles
2021-07-05 Dimensioned drawings
2021-07-05 WQ57 mounting plate
2021-07-05 Resnik in WQ55 box: too small?
2021-07-05 Too small to be practical
2021-07-05 Organized for WH-16 and WQ-57 boxes
2021-07-05 3 years old: Deprecated
2021-07-05 v0.4/deprecated
2021-07-05 Moved to RockBLOCK-feather repo
2021-07-05 Okapi name change
2021-07-05 Manual merge
2021-07-05 Two more Resnik --> Okapi
2021-07-05 Add dimension lines
2021-07-05 Okapi naming
2021-07-05 Comment out libraries that are not in our standard bundle
2021-07-05 Use our MPC4725 library mod (NW interface)
2021-07-05 Updated for MCP23108; left deliberately incomplete (which port?)
2021-07-09 dev namesake: Judy Resnik
2021-07-18 "run" capitalization fix in example code
2021-07-19 ISP driver note
2021-07-22 punctuation consistency in field operator's guide
2021-08-08 note consistency changes
2021-08-08 note consistency changes pt. 2
2024-10-14 Updated layout
2024-10-14 Continued layout updates
2024-10-21 CSA layout
2024-10-30 Design updates toward v1.0
2024-10-31 Continued design updates
2024-11-02 v1.0 updates
2026-06-03 Large-box battery mount with strap: used in deployments.
2026-06-03 CAM files, unverified.
